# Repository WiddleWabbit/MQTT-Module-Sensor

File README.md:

# MQTT Module - Current Sensors

*Currently In Testing - Not Yet Tested*

This module is a plug-in board for the [MQTT Modular Controller Board](https://github.com/WiddleWabbit/MQTT-ModularControllerBoard). It powers and reads up to three 4-20mA current sensors with high-side sensing at approximately 25V, providing 15-bit resolution measurements.

## Features

- Supports up to 3 x 4-20mA sensors (high-side sensing)
- 15-bit resolution via ADS1115 ADC
- On-board ~25V boost converter from 12V input (TPS61170)
- ATmega328PB microcontroller for local control and communication
- Precision 0.1% shunt resistors with low temperature coefficient (25ppm/°C)
- Basic short-circuit protection using PTCs and TVS diodes
- I2C communication with motherboard and internal ADC

## Architecture

The module is built around an **ATmega328PB-A** microcontroller. It interfaces with the motherboard via I2C (SDA on PE1, SCL on PE0) and uses a dedicated I2C bus for the **ADS1115** ADC (base address 0x48, SDA on PC4, SCL on PC5).

### Power
- Utilises 12V input from motherboard, boosted to ~25V using TI TPS61170 (WEBENCH design) with shielded inductor for reduced EMI
- Powers up to three 4-20mA sensors using this 25V.
- Also utilises the 3.3V from the motherboard.
- Maximum 25V current draw should be less than 200mA.
- Maximum 3.3V current draw should be less than 200mA.

### Sensor Interface
- TP5551 OpAmps in servo configuration for accurate current-to-voltage conversion
- 1.5uF capacitors for signal smoothing
- 0.1% precision shunt resistors with a low 25ppm/°C

### Protection
- PTC resettable fuses on sensors trigger at ~150mA
- TVS diodes for overvoltage clamping (trigger at 13V, clamp to 21.5V)
- Shunt rated for 21.5V for five seconds

### Pinout and Connections
- **Motherboard I2C**: SDA (PE1), SCL (PE0)
- **Internal ADC I2C**: SDA (PC4), SCL (PC5)
- **SNS pin** (motherboard sense): PD4
- **General use modular pin**: PD3
- **ISP Programming Header** (2x3, left to right, top to bottom): MISO, VCC, SCK, MOSI, RESET, GND

## Setup and Build

**Firmware**: Not yet implemented. TBA.

**Programming**:
1. Use the 2x3 ISP header to program the ATmega328PB.
2. Connect to an ISP programmer (e.g., USBasp or Arduino as ISP).
3. Firmware will handle sensor readings, ADC configuration, and I2C communication with the motherboard.

**Assembly**:
- Populate the board per the KiCad project files.
- Ensure proper orientation when plugging into the motherboard slots.

## License

This documentation is part of MQTT-Module-Sensor Project and is licensed under the CERN Open Hardware Licence Version 2 - Permissive (CERN-OHL-P-2.0). 
You may redistribute and modify this documentation under the terms of the CERN-OHL-P-2.0. 
This documentation is distributed WITHOUT ANY EXPRESS OR IMPLIED WARRANTY, INCLUDING OF MERCHANTABILITY, SATISFACTORY QUALITY AND FITNESS FOR A PARTICULAR PURPOSE. See the CERN-OHL-P-2.0 for applicable conditions.

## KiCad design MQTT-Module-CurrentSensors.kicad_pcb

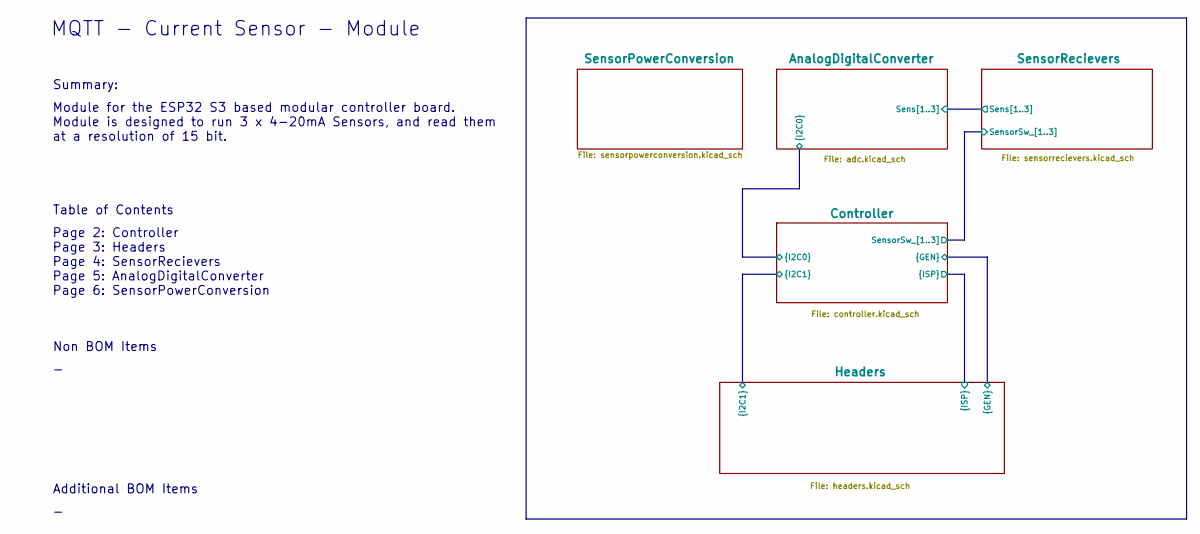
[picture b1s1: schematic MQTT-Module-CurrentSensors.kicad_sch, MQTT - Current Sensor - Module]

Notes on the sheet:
MQTT - Current Sensor - Module
Additional BOM Items
Summary:
Non BOM Items
Page 2: Controller Page 3: Headers Page 4: SensorRecievers Page 5: AnalogDigitalConverter Page 6: SensorPowerConversion
Table of Contents
Module for the ESP32 S3 based modular controller board. Module is designed to run 3 x 4-20mA Sensors, and read them at a resolution of 15 bit.

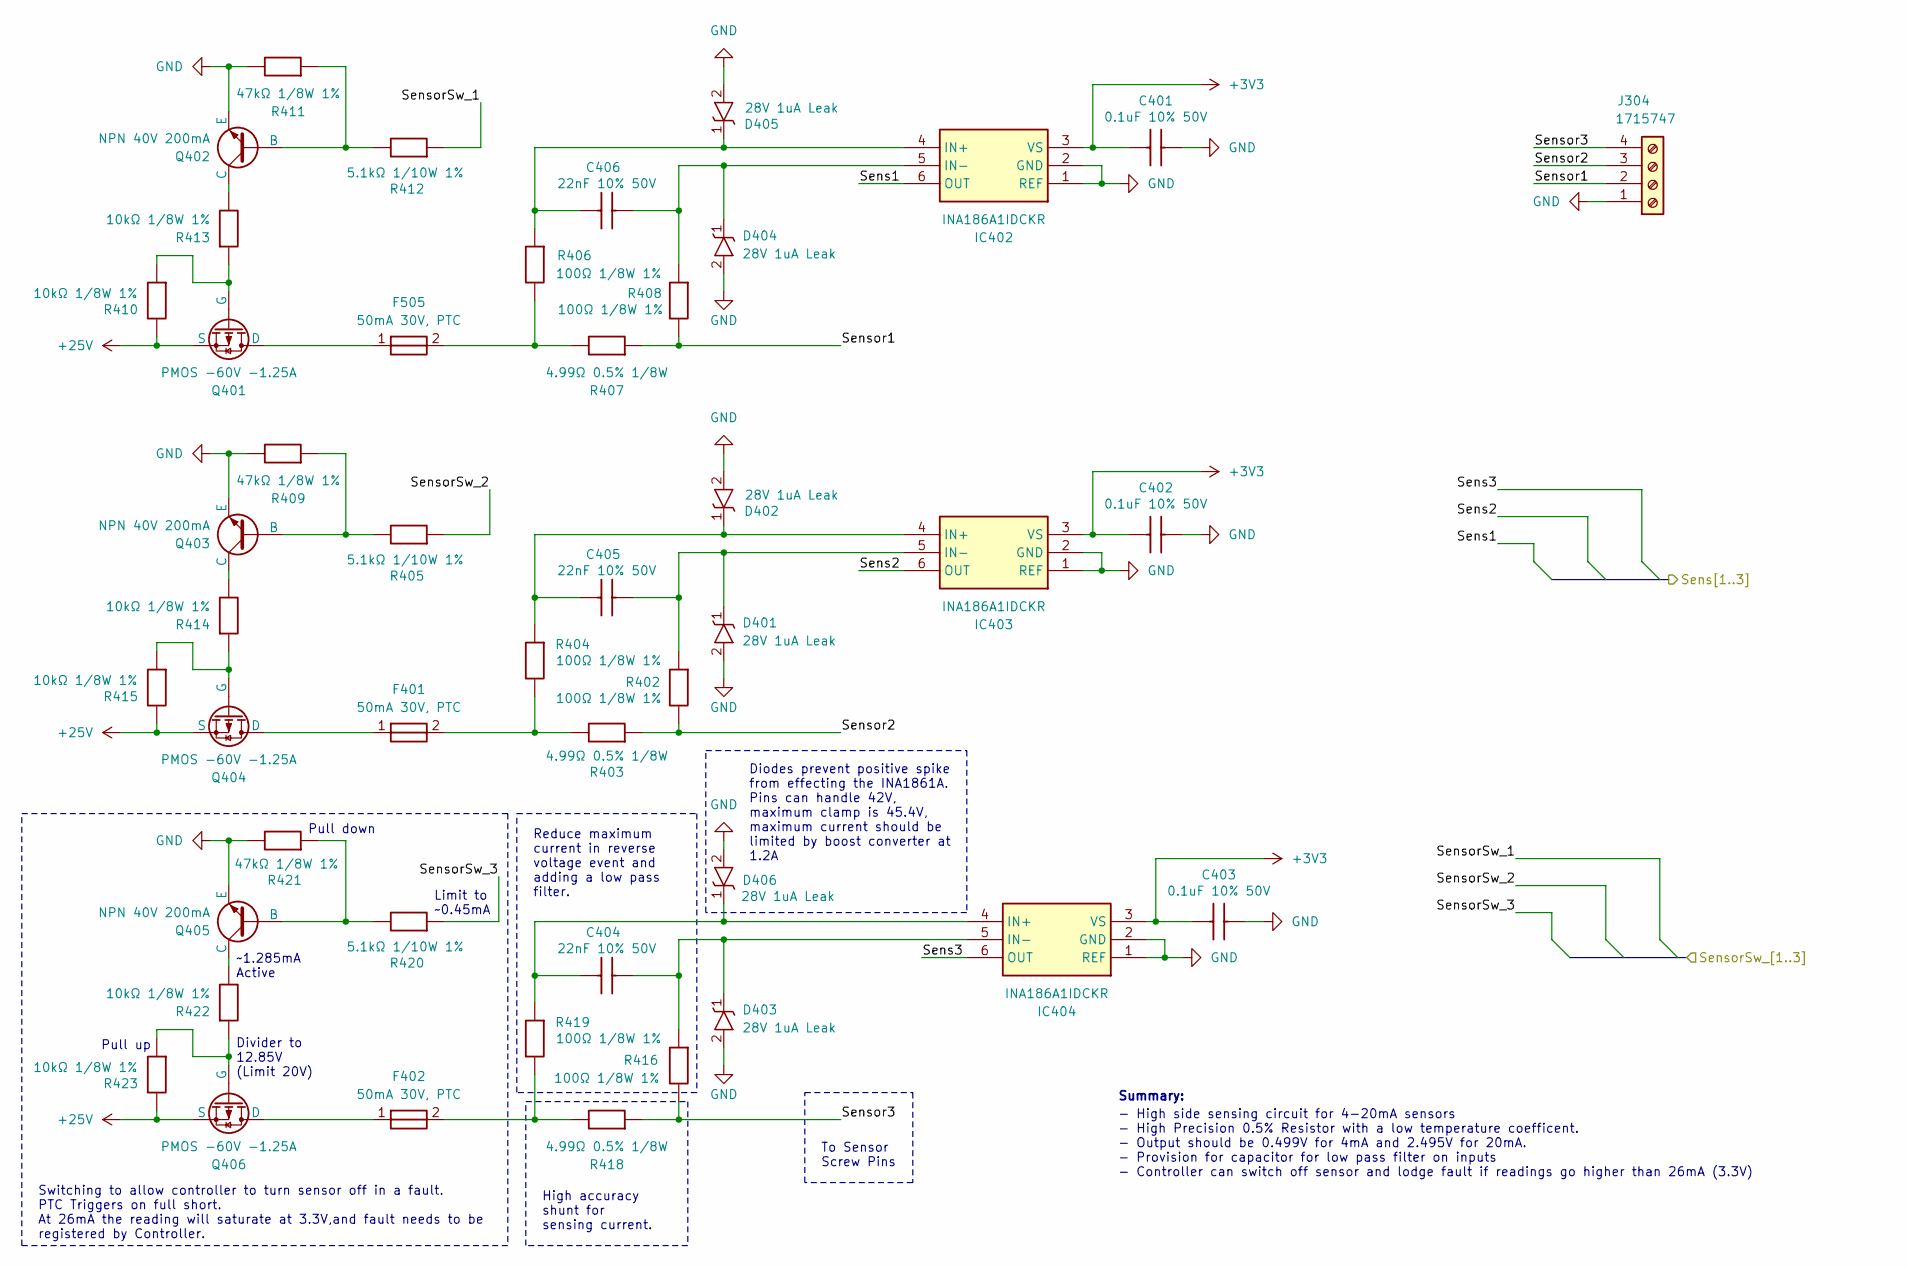
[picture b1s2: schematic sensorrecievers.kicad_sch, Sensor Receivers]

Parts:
C401, C402, C403: 0.1uF 10% 50V; CAPC1608X90N; Mouser Part Number 603-CC603KRX7R9BB104
C404, C405, C406: 22nF 10% 50V; CAPC1608X90N; Manufacturer Part No CL10B223KB8NNNC; JLCPCB Part # C21122
D401, D402, D403, D404, D405, D406: 28V 1uA Leak; SODFL3619X98N; Manufacturer Part No SMF28A; JLCPCB Part # C720061
F401, F402, F505: 50mA 30V, PTC; FUSC3226X110N; Mouser Part Number 652-MF-USMF005-2
IC402, IC403, IC404: INA186A1IDCKR; SOT65P210X110-6N; Mouser Part Number 595-INA186A1IDCKR
J304: 1715747; Mouser Part Number 651-1715747
Q401, Q404, Q406: PMOS -60V -1.25A; SOT-23-3 - FDN5618P; Manufacturer Part No FDN5618P; JLCPCB Part # C400792
Q402, Q403, Q405: NPN 40V 200mA; SOT-23; Manufacturer Part No MMBT3904LT1G; JLCPCB Part # C81464
R402, R404, R406, R408, R416, R419: 100Ω 1/8W 1%; RESC2013X65N; Mouser Part Number 303-0805W8F1000T5E
R403, R407, R418: 4.99Ω 0.5% 1/8W; Generic-0603; Mouser Part Number 71-TNPW06034R99DEEA
R405, R412, R420: 5.1kΩ 1/10W 1%; RESC1608X55N; Mouser Part Number 303-0603WAF5101T5E
R409, R411, R421: 47kΩ 1/8W 1%; RESC2013X65N; Manufacturer Part No 0805W8F4702T5E; JLCPCB Part # C17713
R410, R413, R414, R415, R422, R423: 10kΩ 1/8W 1%; RESC2013X65N; Mouser Part Number 303-0805W8F1002T5E

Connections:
+3V3: C401.1, C402.1, C403.1, IC402.3 (VS), IC403.3 (VS), IC404.3 (VS); also elsewhere on the board
+25V: Q401.2 (S), Q404.2 (S), Q406.2 (S), R410.2, R415.2, R423.2; also elsewhere on the board
/AnalogDigitalConverter/Sens1: IC402.6 (OUT); also elsewhere on the board
/AnalogDigitalConverter/Sens2: IC403.6 (OUT); also elsewhere on the board
/AnalogDigitalConverter/Sens3: IC404.6 (OUT); also elsewhere on the board
/Controller/SensorSw_1: R412.1; also elsewhere on the board
/Controller/SensorSw_2: R405.1; also elsewhere on the board
/Controller/SensorSw_3: R420.1; also elsewhere on the board
/SensorRecievers/Sensor1: J304.2, R407.1, R408.2
/SensorRecievers/Sensor2: J304.3, R402.2, R403.1
/SensorRecievers/Sensor3: J304.4, R416.2, R418.1
GND: C401.2, C402.2, C403.2, D401.2 (A2), D402.2 (A2), D403.2 (A2), D404.2 (A2), D405.2 (A2), D406.2 (A2), IC402.1 (REF), IC402.2 (GND), IC403.1 (REF), IC403.2 (GND), IC404.1 (REF), IC404.2 (GND), J304.1, Q402.2 (E), Q403.2 (E), Q405.2 (E), R409.2, R411.2, R421.2; also elsewhere on the board
unnamed: C405.2, D401.1 (A1), IC403.5 (IN-), R402.1
unnamed: C405.1, D402.1 (A1), IC403.4 (IN+), R404.1
unnamed: C404.2, D403.1 (A1), IC404.5 (IN-), R416.1
unnamed: C406.2, D404.1 (A1), IC402.5 (IN-), R408.1
unnamed: C406.1, D405.1 (A1), IC402.4 (IN+), R406.1
unnamed: C404.1, D406.1 (A1), IC404.4 (IN+), R419.1
unnamed: F401.2, R403.2, R404.2
unnamed: F402.2, R418.2, R419.2
unnamed: F505.2, R406.2, R407.2
unnamed: F505.1, Q401.3 (D)
unnamed: Q401.1 (G), R410.1, R413.1
unnamed: Q402.1 (B), R411.1, R412.2
unnamed: Q402.3 (C), R413.2
unnamed: Q403.1 (B), R405.2, R409.1
unnamed: Q403.3 (C), R414.2
unnamed: F401.1, Q404.3 (D)
unnamed: Q404.1 (G), R414.1, R415.1
unnamed: Q405.1 (B), R420.2, R421.1
unnamed: Q405.3 (C), R422.2
unnamed: F402.1, Q406.3 (D)
unnamed: Q406.1 (G), R422.1, R423.1

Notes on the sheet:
Switching to allow controller to turn sensor off in a fault. PTC Triggers on full short. At 26mA the reading will saturate at 3.3V,and fault needs to be registered by Controller.
Pull down
Pull up
Reduce maximum current in reverse voltage event and adding a low pass filter.
Diodes prevent positive spike from effecting the INA1861A. Pins can handle 42V, maximum clamp is 45.4V, maximum current should be limited by boost converter at 1.2A
Limit to ~0.45mA
To Sensor Screw Pins
- High side sensing circuit for 4-20mA sensors - High Precision 0.5% Resistor with a low temperature coefficent. - Output should be 0.499V for 4mA and 2.495V for 20mA. - Provision for capacitor for low pass filter on inputs - Controller can switch off sensor and lodge fault if readings go higher th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
~1.285mA Active
Summary:
High accuracy shunt for sensing current.
Divider to 12.85V (Limit 20V)

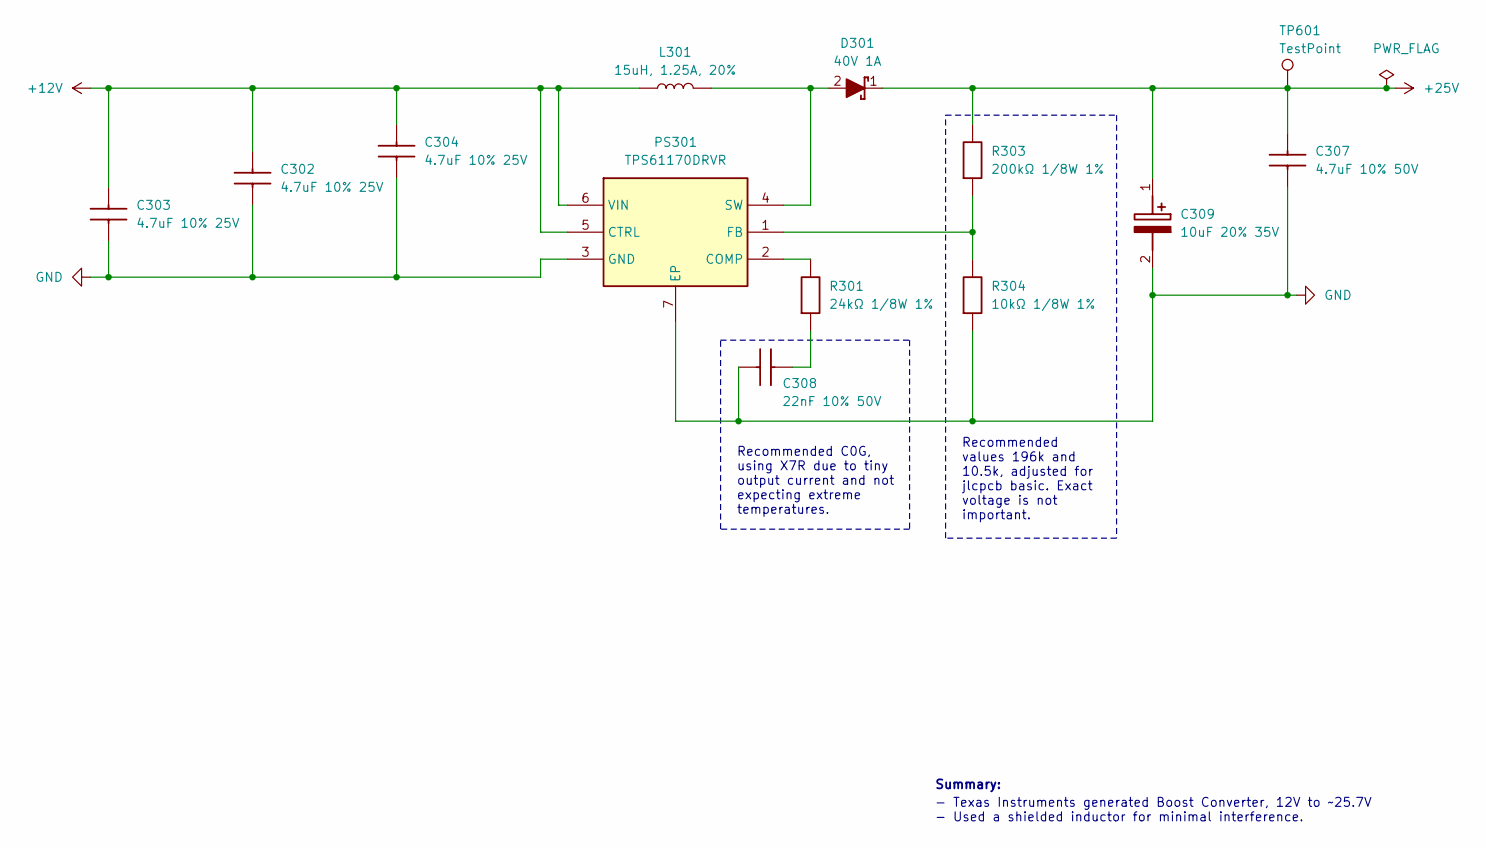
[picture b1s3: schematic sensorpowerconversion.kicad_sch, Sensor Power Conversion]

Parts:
C302, C303, C304: 4.7uF 10% 25V; CAPC2012X140N; Mouser Part Number 187-CL21A475KAQNNNE
C307: 4.7uF 10% 50V; CAPC3216X180N; Manufacturer Part No 1206B475K500NT; JLCPCB Part # C29823
C308: 22nF 10% 50V; CAPC2012X75N; Manufacturer Part No CL21B223KBANNNC; JLCPCB Part # C1729
C309: 10uF 20% 35V; EEE0GA101SR; Mouser Part Number 667-EEE-FK1V100R
D301: 40V 1A; D_SOD-323F; Manufacturer Part No 1N5819WS; JLCPCB Part # C191023
L301: 15uH, 1.25A, 20%; INDM4040X190N; Mouser Part Number 70-IFSC1515AHER150M0
PS301: TPS61170DRVR; SON65P200X200X80-7N; Mouser Part Number 595-TPS61170DRVR
R301: 24kΩ 1/8W 1%; RESC2013X65N; Manufacturer_Part_Number 0805W8F2402T5E; JLCPCB Part # C17575
R303: 200kΩ 1/8W 1%; RESC2013X65N; Manufacturer Part No 0805W8F2003T5E; JLCPCB Part # C17539
R304: 10kΩ 1/8W 1%; RESC2013X65N; Mouser Part Number 303-0805W8F1002T5E
TP601: TestPoint; TestPoint_Pad_2.0x2.0mm

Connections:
+12V: C302.2, C303.2, C304.2, L301.1, PS301.5 (CTRL), PS301.6 (VIN); also elsewhere on the board
+25V: C307.2, C309.1 (+), D301.1 (K), R303.2, TP601.1; also elsewhere on the board
GND: C302.1, C303.1, C304.1, C307.1, C308.1, C309.2 (-), PS301.3 (GND), PS301.7 (EP), R304.1; also elsewhere on the board
unnamed: C308.2, R301.1
unnamed: D301.2 (A), L301.2, PS301.4 (SW)
unnamed: PS301.2 (COMP), R301.2
unnamed: PS301.1 (FB), R303.1, R304.2

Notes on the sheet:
- Texas Instruments generated Boost Converter, 12V to ~25.7V - Used a shielded inductor for minimal interference.
Recommended values 196k and 10.5k, adjusted for jlcpcb basic. Exact voltage is not important.
Recommended C0G, using X7R due to tiny output current and not expecting extreme temperatures.
Summary:

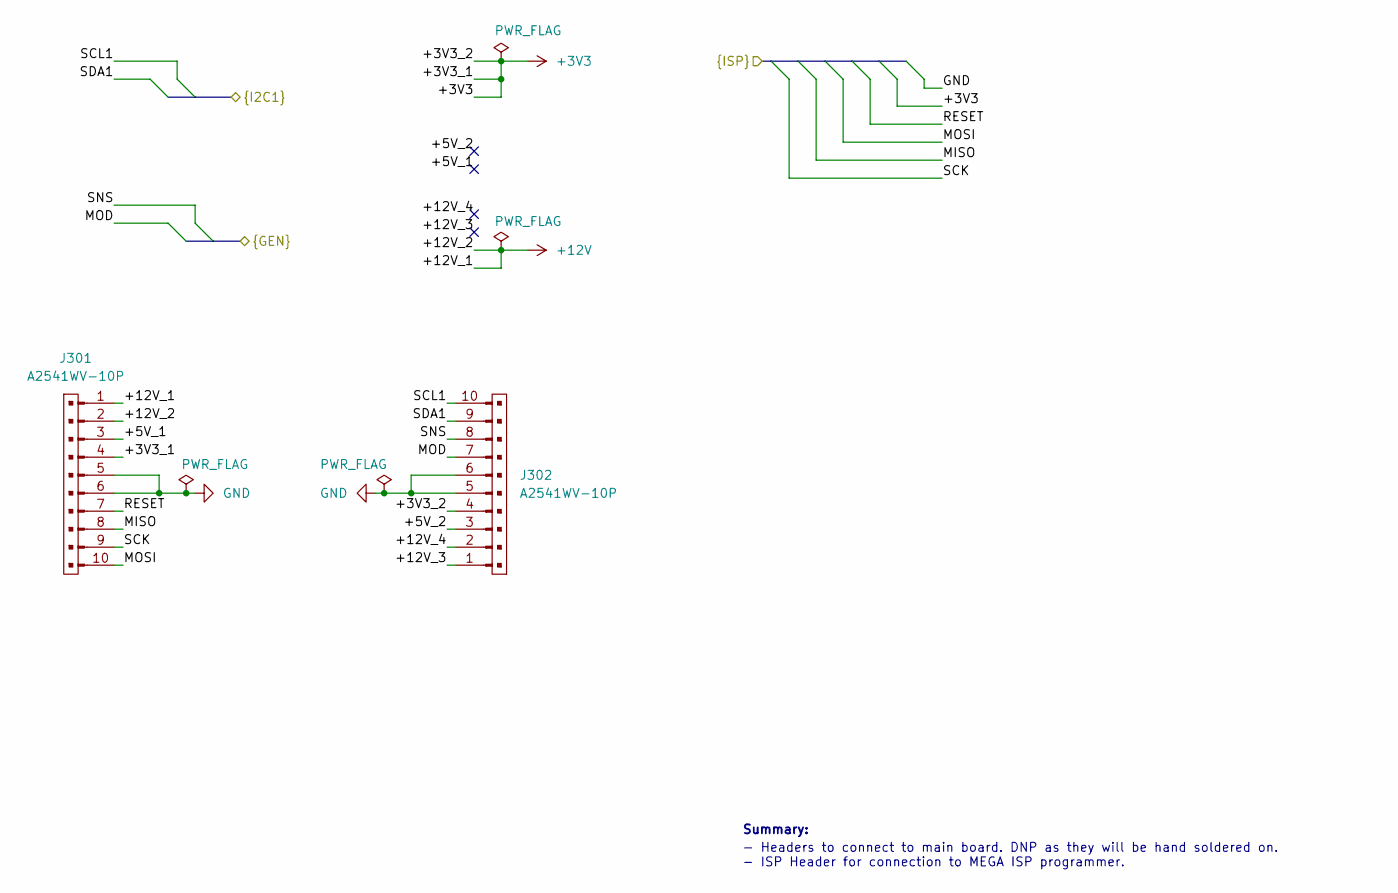
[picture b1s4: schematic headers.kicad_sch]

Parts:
J301, J302: A2541WV-10P; PinHeader_1x10_P2.54mm_Vertical_Male; Manufacturer Part No A2541WV-10P; JLCPCB Part # C225485

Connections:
+3V3: J301.4, J302.4; also elsewhere on the board
+12V: J301.1, J301.2; also elsewhere on the board
/Controller/MISO: J301.8; also elsewhere on the board
/Controller/MOD: J302.7; also elsewhere on the board
/Controller/MOSI: J301.10; also elsewhere on the board
/Controller/RESET: J301.7; also elsewhere on the board
/Controller/SCK: J301.9; also elsewhere on the board
/Controller/SCL1: J302.10; also elsewhere on the board
/Controller/SDA1: J302.9; also elsewhere on the board
/Controller/SNS: J302.8; also elsewhere on the board
/Headers/+5V_1: J301.3
/Headers/+5V_2: J302.3
/Headers/+12V_3: J302.1
/Headers/+12V_4: J302.2
GND: J301.5, J301.6, J302.5, J302.6; also elsewhere on the board

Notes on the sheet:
Summary:
- Headers to connect to main board. DNP as they will be hand soldered on. - ISP Header for connection to MEGA ISP programmer.

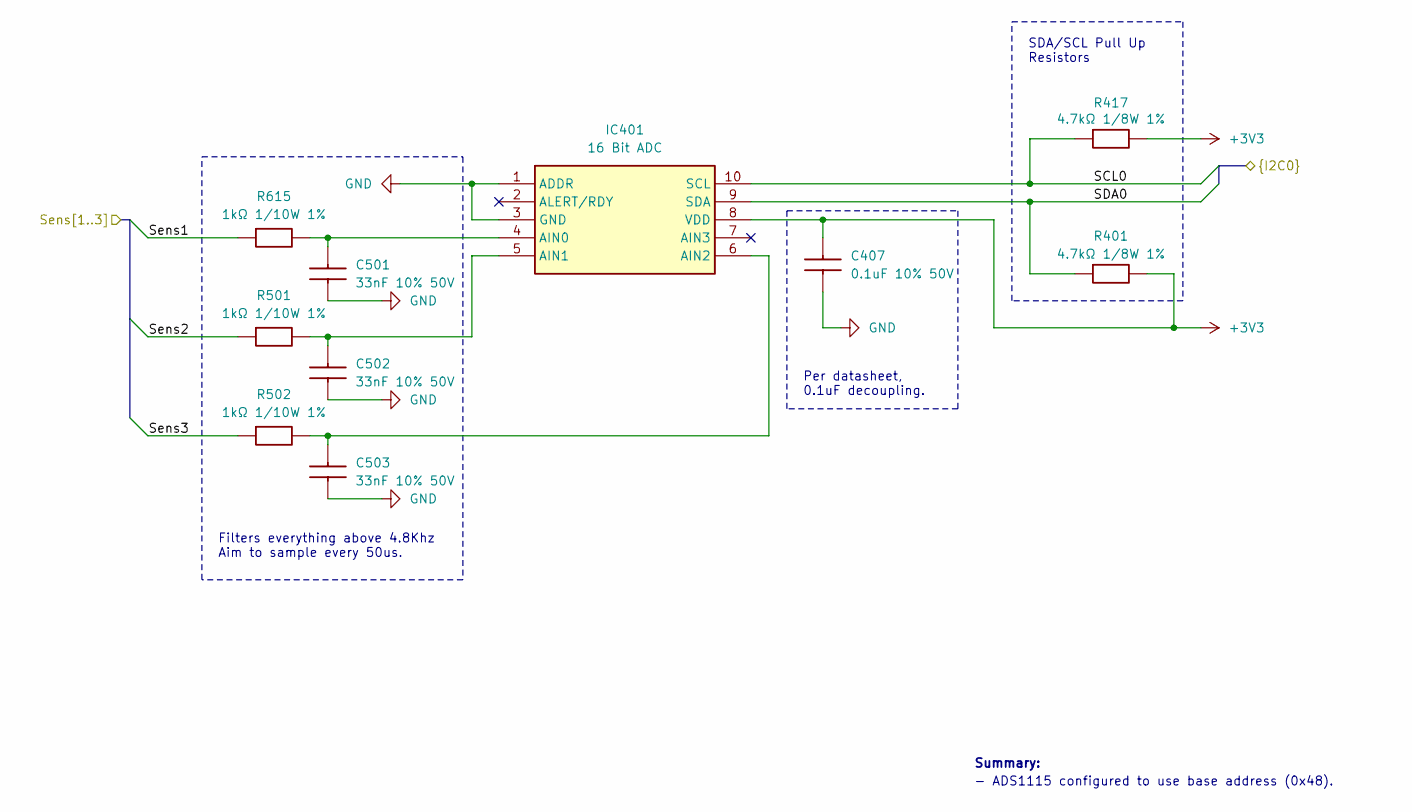
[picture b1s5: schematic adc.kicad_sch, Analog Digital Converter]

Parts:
C407: 0.1uF 10% 50V; CAPC1608X90N; Mouser Part Number 603-CC603KRX7R9BB104
C501, C502, C503: 33nF 10% 50V; CAPC1608X90N; Manufacturer Part No CL10B333KB8NNNC; JLCPCB Part # C21117
IC401: 16 Bit ADC; SOP50P490X110-10N; Mouser Part Number 595-ADS1115IDGST
R401, R417: 4.7kΩ 1/8W 1%; RESC2013X65N; Mouser Part Number 303-0805W8F4701T5E
R501, R502, R615: 1kΩ 1/10W 1%; RESC1608X55N; Manufacturer Part No 0603WAF1001T5E; JLCPCB Part # C21190

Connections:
+3V3: C407.2, IC401.8 (VDD), R401.2, R417.2; also elsewhere on the board
/AnalogDigitalConverter/SCL0: IC401.10 (SCL), R417.1; also elsewhere on the board
/AnalogDigitalConverter/SDA0: IC401.9 (SDA), R401.1; also elsewhere on the board
/AnalogDigitalConverter/Sens1: R615.1; also elsewhere on the board
/AnalogDigitalConverter/Sens2: R501.1; also elsewhere on the board
/AnalogDigitalConverter/Sens3: R502.1; also elsewhere on the board
GND: C407.1, C501.1, C502.1, C503.1, IC401.1 (ADDR), IC401.3 (GND); also elsewhere on the board
unnamed: C501.2, IC401.4 (AIN0), R615.2
unnamed: C502.2, IC401.5 (AIN1), R501.2
unnamed: C503.2, IC401.6 (AIN2), R502.2

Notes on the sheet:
Filters everything above 4.8Khz Aim to sample every 50us.
SDA/SCL Pull Up Resistors
- ADS1115 configured to use base address (0x48).
Per datasheet, 0.1uF decoupling.
Summary:

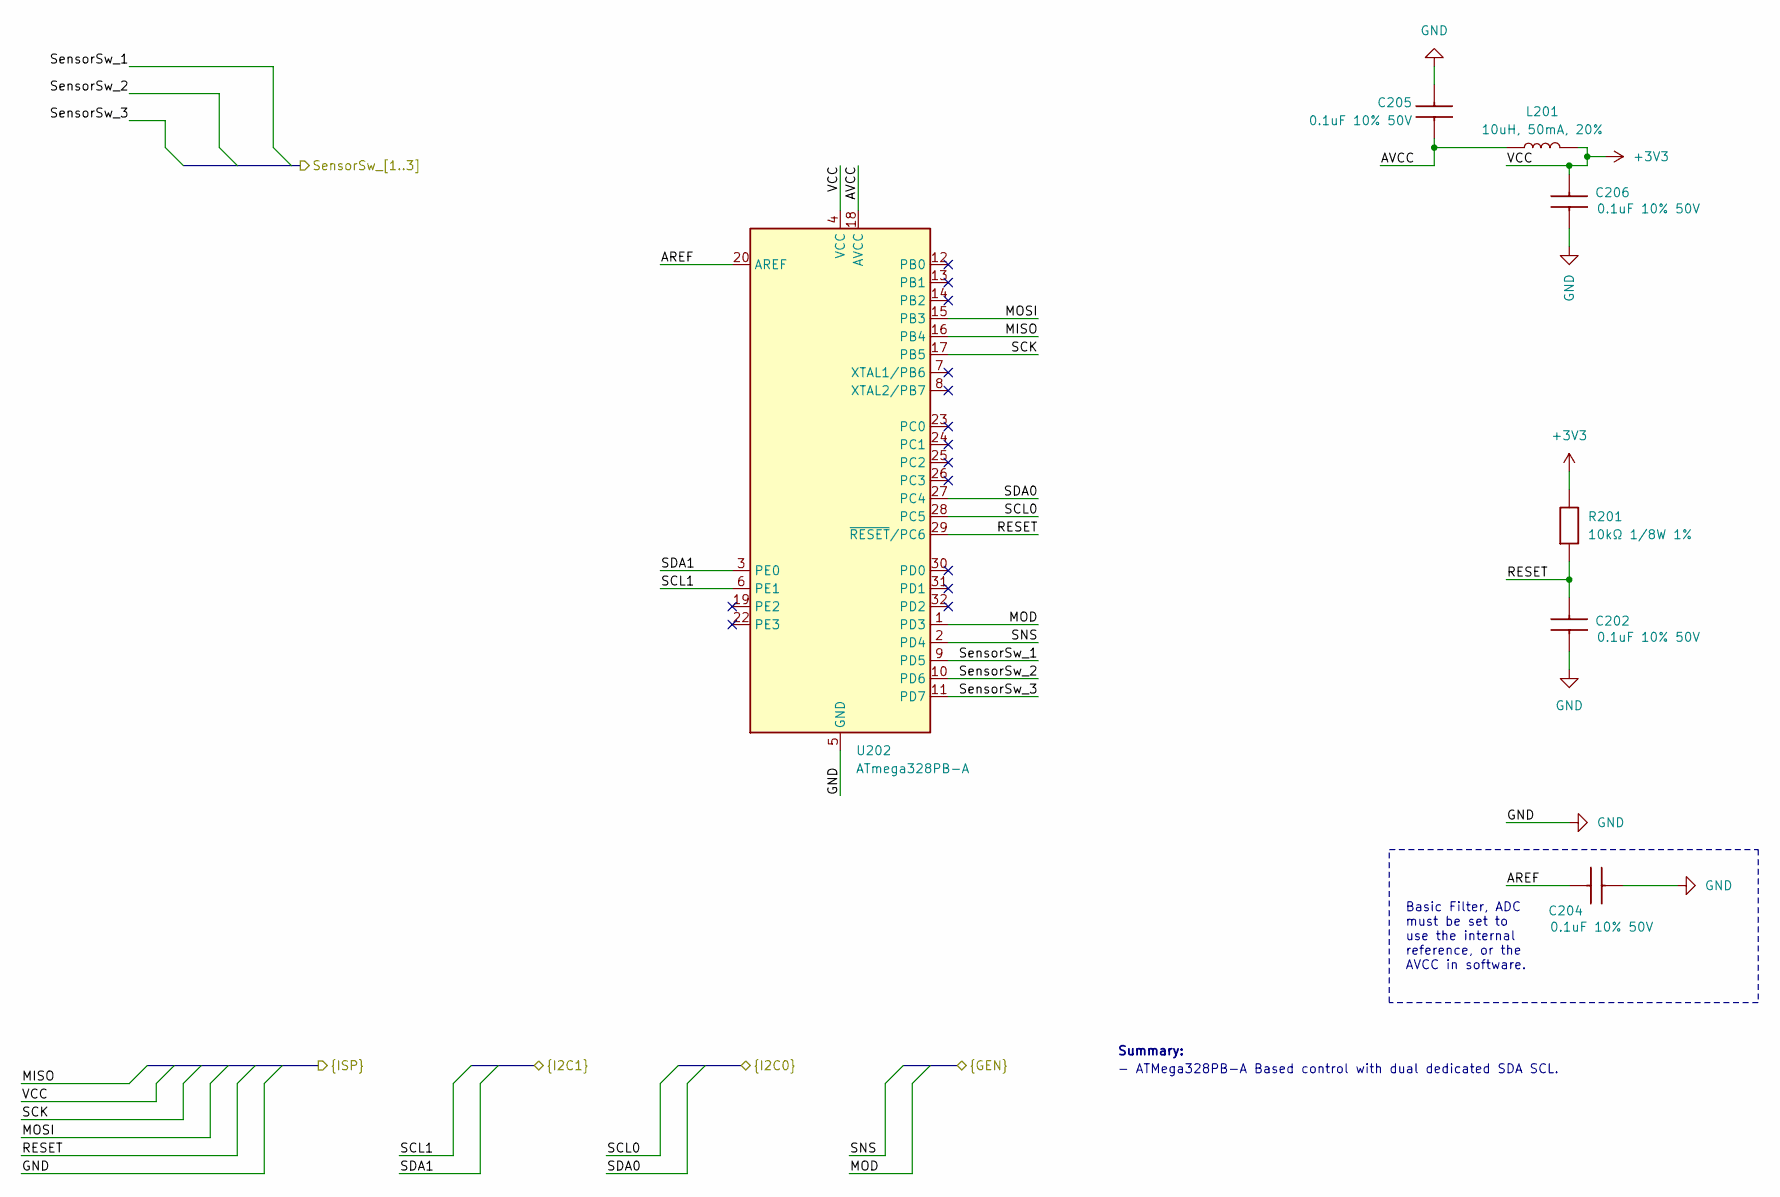
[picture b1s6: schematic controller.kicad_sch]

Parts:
C202, C204, C205, C206: 0.1uF 10% 50V; CAPC1608X90N; Mouser Part Number 603-CC603KRX7R9BB104
L201: 10uH, 50mA, 20%; L_0603_1608Metric; Manufacturer Part No MCL1608S100MT; JLCPCB Part # C51942
R201: 10kΩ 1/8W 1%; RESC2013X65N; Mouser Part Number 303-0805W8F1002T5E
U202: ATmega328PB-A; TQFP-32_7x7mm_P0.8mm; Manufacturer Part No ATMEGA328PB-AU; JLCPCB Part # C132230

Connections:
+3V3: C206.2, L201.2, R201.2, U202.4 (VCC); also elsewhere on the board
/AnalogDigitalConverter/SCL0: U202.28 (PC5); also elsewhere on the board
/AnalogDigitalConverter/SDA0: U202.27 (PC4); also elsewhere on the board
/Controller/AREF: C204.1, U202.20 (AREF)
/Controller/AVCC: C205.1, L201.1, U202.18 (AVCC)
/Controller/MISO: U202.16 (PB4); also elsewhere on the board
/Controller/MOD: U202.1 (PD3); also elsewhere on the board
/Controller/MOSI: U202.15 (PB3); also elsewhere on the board
/Controller/RESET: C202.1, R201.1, U202.29 (~RESET/PC6); also elsewhere on the board
/Controller/SCK: U202.17 (PB5); also elsewhere on the board
/Controller/SCL1: U202.6 (PE1); also elsewhere on the board
/Controller/SDA1: U202.3 (PE0); also elsewhere on the board
/Controller/SNS: U202.2 (PD4); also elsewhere on the board
/Controller/SensorSw_1: U202.9 (PD5); also elsewhere on the board
/Controller/SensorSw_2: U202.10 (PD6); also elsewhere on the board
/Controller/SensorSw_3: U202.11 (PD7); also elsewhere on the board
GND: C202.2, C204.2, C205.2, C206.1, U202.5 (GND), U202.21 (GND); also elsewhere on the board

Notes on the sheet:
Basic Filter, ADC must be set to use the internal reference, or the AVCC in software.
- ATMega328PB-A Based control with dual dedicated SDA SCL.
Summary:

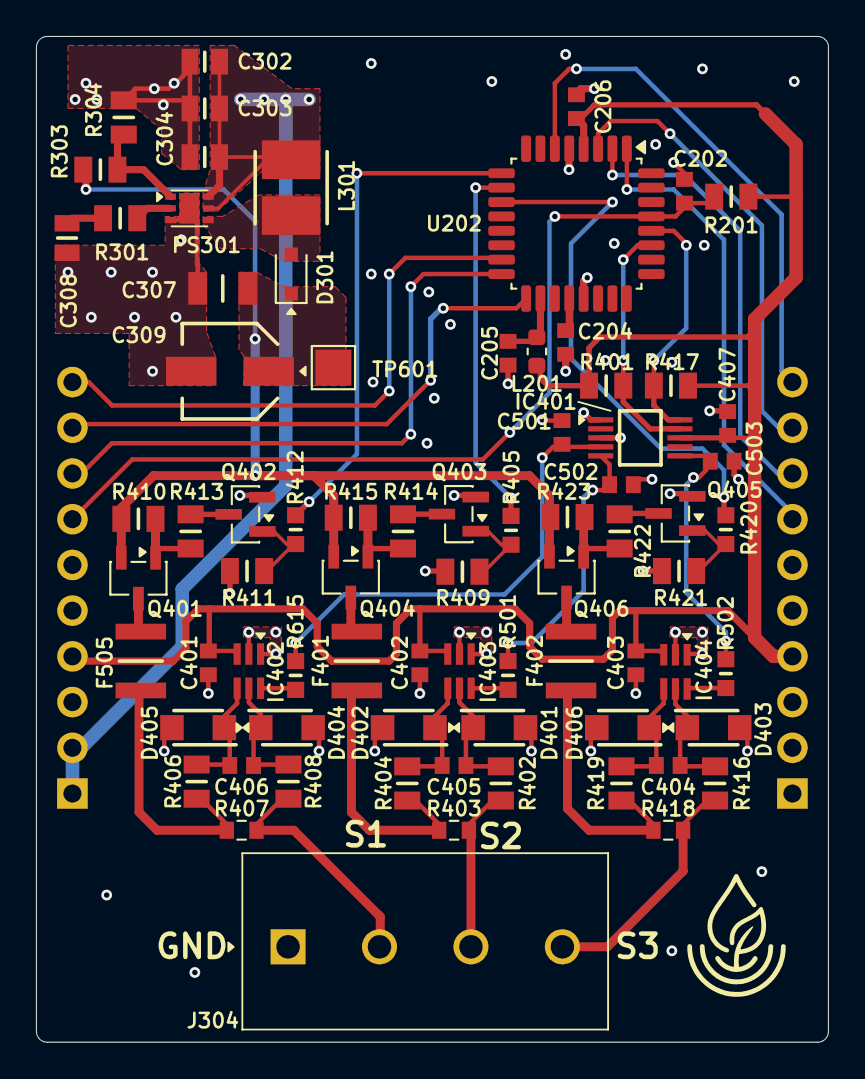
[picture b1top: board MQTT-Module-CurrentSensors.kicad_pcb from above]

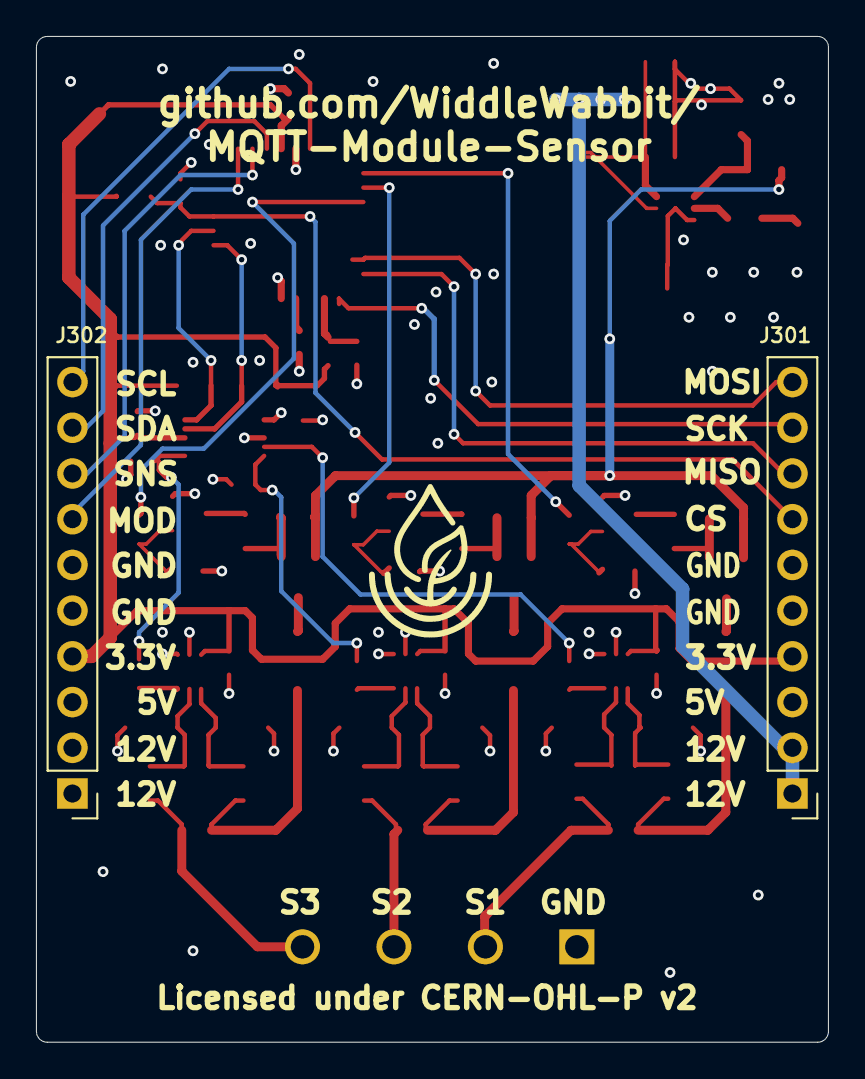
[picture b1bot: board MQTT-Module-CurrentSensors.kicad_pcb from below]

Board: 4 copper layers, 44.0 x 55.9 mm, 78 parts (2 on the bottom side), 53 nets.

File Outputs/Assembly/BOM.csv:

"#","Qty","Reference","Value","Manufacturer","Manufacturer Part No","JLCPCB Part #","Package","Footprint"
"1","8","C202,C204,C205,C206,C401,C402,C403,C407","0.1uF 10% 50V","YAGEO","CC0603KRX7R9BB104","C14663","0603","JLCPCB Basic:CAPC1608X90N"
"2","3","C302,C303,C304","4.7uF 10% 25V","Samsung Electro-Mechanics","CL21A475KAQNNNE","C1779","0805","JLCPCB Basic:CAPC2012X140N"
"3","1","C307","4.7uF 10% 50V","FH (Guangdong Fenghua Advanced Tech)","1206B475K500NT","C29823","1206","JLCPCB Basic:CAPC3216X180N"
"4","1","C308","22nF 10% 50V","Samsung Electro-Mechanics","CL21B223KBANNNC","C1729","0805","JLCPCB Basic:CAPC2012X75N"
"5","1","C309","10uF 20% 35V","PANASONIC","EEEFK1V100R","C336198","SMD","PANASONIC Capacitors:EEE0GA101SR"
"6","3","C404,C405,C406","22nF 10% 50V","Samsung Electro-Mechanics","CL10B223KB8NNNC","C21122","0603","JLCPCB Basic:CAPC1608X90N"
"7","3","C501,C502,C503","33nF 10% 50V","Samsung Electro-Mechanics","CL10B333KB8NNNC","C21117","0603","JLCPCB Basic:CAPC1608X90N"
"8","1","D301","40V 1A","Guangdong Hottech","1N5819WS","C191023","SOD-323","GUANGDONG HOTTECH Diodes:D_SOD-323F"
"9","6","D401,D402,D403,D404,D405,D406","28V 1uA Leak","Littelfuse","SMF28A","C720061","SOD-123FL","LITTELFUSE Diodes:SODFL3619X98N"
"10","3","F401,F402,F505","50mA 30V, PTC","BOURNS","MF-USMF005-2","C118758","1210","BOURNS Fuses:FUSC3226X110N"
"11","1","IC401","16 Bit ADC","Texas Instruments","ADS1115IDGST","C468683","VSSOP-10-0.5mm","TEXAS INSTRUMENTS ICs:SOP50P490X110-10N"
"12","3","IC402,IC403,IC404","INA186A1IDCKR","TI","INA186A1IDCKR","C2058311","SC-70-6","TEXAS INSTRUMENTS ICs:SOT65P210X110-6N"
"13","2","J301,J302","A2541WV-10P","CJT(Changjiang Connectors)","A2541WV-10P","C225485","Plugin,P=2.54mm","CJT Connectors:PinHeader_1x10_P2.54mm_Vertical_Male"
"14","1","J304","1715747","Phoenix Contact","1715747","C5443561","P=5.08mm","PHOENIX CONTACT Terminals:1715747"
"15","1","L201","10uH, 50mA, 20%","Sunlord","MCL1608S100MT","C51942","0603","SUNLORD Inductors:L_0603_1608Metric"
"16","1","L301","15uH, 1.25A, 20%","Vishay Intertech","IFSC1515AHER150M01","C844950","SMD,4x4mm","VISHAY INTERTECH Inductors:INDM4040X190N"
"17","1","PS301","TPS61170DRVR","Texas Instruments","TPS61170DRVR","C15163","WSON-6(2x2)","TEXAS INSTRUMENTS ICs:SON65P200X200X80-7N"
"18","3","Q401,Q404,Q406","PMOS -60V -1.25A","onsemi","FDN5618P","C400792","SOT-23-3","ONSEMI Transistors:SOT-23-3 - FDN5618P"
"19","3","Q402,Q403,Q405","NPN 40V 200mA","onsemi","MMBT3904LT1G","C81464","SOT-23","ONSEMI Transistors:SOT-23"
"20","8","R201,R304,R410,R413,R414,R415,R422,R423","10kΩ 1/8W 1%","UNI-ROYAL(Uniroyal Elec)","0805W8F1002T5E","C17414","0805","JLCPCB Basic:RESC2013X65N"
"21","1","R301","24kΩ 1/8W 1%","UNI-ROYAL(Uniroyal Elec)","0805W8F2402T5E","C17575","0805","JLCPCB Basic:RESC2013X65N"
"22","1","R303","200kΩ 1/8W 1%","UNI-ROYAL(Uniroyal Elec)","0805W8F2003T5E","C17539","0805","JLCPCB Basic:RESC2013X65N"
"23","2","R401,R417","4.7kΩ 1/8W 1%","UNI-ROYAL(Uniroyal Elec)","0805W8F4701T5E"," C17673","0805","JLCPCB Basic:RESC2013X65N"
"24","6","R402,R404,R406,R408,R416,R419","100Ω 1/8W 1%","UNI-ROYAL(Uniroyal Elec)","0805W8F1000T5E","C17408","0805","JLCPCB Basic:RESC2013X65N"
"25","3","R403,R407,R418","4.99Ω 0.5% 1/8W","Vishay Intertech","TNPW06034R99DEEA","C1857702","0603","JLCPCB Basic:Generic-0603"
"26","3","R405,R412,R420","5.1kΩ 1/10W 1%","UNI-ROYAL(Uniroyal Elec)","0603WAF5101T5E","C23186","0603","JLCPCB Basic:RESC1608X55N"
"27","3","R409,R411,R421","47kΩ 1/8W 1%","UNI-ROYAL(Uniroyal Elec)","0805W8F4702T5E","C17713","0805","JLCPCB Basic:RESC2013X65N"
"28","3","R501,R502,R615","1kΩ 1/10W 1%","UNI-ROYAL(Uniroyal Elec)","0603WAF1001T5E","C21190","0603","JLCPCB Basic:RESC1608X55N"
"29","1","U202","ATmega328PB-A","Microchip Tech","ATMEGA328PB-AU","C132230","TQFP-32(7x7)","Package_QFP:TQFP-32_7x7mm_P0.8mm"

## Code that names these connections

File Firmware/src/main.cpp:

#include <Arduino.h>

#include "AvrAds1115.h"
#include "AvrEeprom.h"
#include "AvrInterruptMask.h"
#include "AvrSensorSwitchPort.h"
#include "AvrTwi1Slave.h"
#include "ModuleLink.h"
#include "ModuleProtocol.h"
#include "SensorInputs.h"


// ========== Board pins ==========

// Motherboard bus is schematic I2C1. It is the chip's TWI1 peripheral:
// PE0 is SDA and PE1 is SCL. Wire1 owns these pins in hardware.
const uint8_t SDA_PIN = 23;
const uint8_t SCL_PIN = 24;
const uint8_t MOD_PIN = 3;
const uint8_t SNS_PIN = 4;

// SensorSw drives the NPN that turns on that channel's high-side PMOS.
// High closes the loop. The base pulldown holds it open until a set-on.
const uint8_t SENSOR_SW1_PIN = 5;
const uint8_t SENSOR_SW2_PIN = 6;
const uint8_t SENSOR_SW3_PIN = 7;

// ADC bus is schematic I2C0. It is the chip's TWI0 peripheral.
// PC4 is SDA and PC5 is SCL. Wire owns these pins in hardware.
const uint8_t ADC_SDA_PIN = 18;
const uint8_t ADC_SCL_PIN = 19;

static_assert(SDA_PIN == 23, "PE0 is motherboard SDA.");
static_assert(SCL_PIN == 24, "PE1 is motherboard SCL.");
static_assert(MOD_PIN == 3, "PD3 is MOD.");
static_assert(SNS_PIN == 4, "PD4 is SNS.");
static_assert(SENSOR_SW1_PIN == 5, "PD5 is SensorSw_1.");
static_assert(SENSOR_SW2_PIN == 6, "PD6 is SensorSw_2.");
static_assert(SENSOR_SW3_PIN == 7, "PD7 is SensorSw_3.");
static_assert(ADC_SDA_PIN == 18, "PC4 is ADC SDA.");
static_assert(ADC_SCL_PIN == 19, "PC5 is ADC SCL.");


// ========== Product settings ==========

const uint16_t MODULE_TYPE = module_protocol::kTypeSensorModule;

// Identity firmware bytes are board revision, then firmware revision.
const uint8_t BOARD_REVISION = 3;
const uint8_t FIRMWARE_REVISION = 1;
const uint16_t FIRMWARE_VERSION =
    static_cast<uint16_t>((static_cast<uint16_t>(BOARD_REVISION) << 8) |
                          FIRMWARE_REVISION);

// ADDR is strapped to GND on this board.
const uint8_t ADS1115_ADDRESS = 0x48;
const uint8_t SENSOR_COUNT = 3;

// 2400 counts is 0.300 V at GAIN_ONE (125 uV per count). On the
// 4.99 ohm shunt and INA186A1 (25 V/V) that is about 2.4 mA. A live
// 4 mA loop is 3992 counts. An open input sits below this.
const int16_t SENSOR_CONNECTED_MIN_COUNTS = 2400;

// 21956 counts is 2.745 V, 22 mA on that same front end. Two stored
// samples at or above this open the loop and latch a fault.
const int32_t SENSOR_TRIP_COUNTS = 21956;
const uint8_t SENSOR_TRIP_SAMPLES = 2;

// Live samples kept for each input's reading. The window rotates
// once it is full. A shorter run reports the average so far.
const uint8_t SENSOR_AVERAGE_SAMPLES = 25;


// ========== Modules ==========

AvrTwi1Slave moduleSlave;
AvrAds1115 ads(ADS1115_ADDRESS, AvrAds1115::kGainOne,
               AvrAds1115::kRate860Sps);
AvrSensorSwitchPort sensorSwitches(SENSOR_SW1_PIN, SENSOR_SW2_PIN,
                                   SENSOR_SW3_PIN);
AvrInterruptMask interruptMask;
AvrEeprom eeprom;
SensorInputs sensorInputs(ads, sensorSwitches, interruptMask, eeprom,
                          SENSOR_COUNT, SENSOR_CONNECTED_MIN_COUNTS,
                          SENSOR_TRIP_COUNTS, SENSOR_TRIP_SAMPLES,
                          SENSOR_AVERAGE_SAMPLES);
ModuleLink moduleLink(moduleSlave, sensorInputs, MODULE_TYPE, FIRMWARE_VERSION);


// ========== Application ==========

/**
 * Drives SNS low so the motherboard sees this module seated, drives
 * each SensorSw pin low so every loop stays open, and holds MOD as an
 * input with pull-up. The slave stays off until MOD is low. A loop
 * closes only after SET_SENSOR on.
 *
 * @return Nothing.
 */
void setup()
{
  pinMode(SNS_PIN, OUTPUT);
  digitalWrite(SNS_PIN, LOW);
  pinMode(MOD_PIN, INPUT_PULLUP);
  sensorSwitches.begin();
}

/**
 * Advances the ADS1115 scan one step, which also arms at most one
 * fault-image byte, then gates the unconfigured address on MOD. A
 * low MOD enables 0x0A. After SET_ADDRESS the link keeps that
 * address. This loop does not block, so the host's 5 ms MOD gate
 * is met.
 *
 * @return Nothing.
 */
void loop()
{
  sensorInputs.update();
  const bool modIsLow = digitalRead(MOD_PIN) == LOW;
  moduleLink.update(modIsLow);
}

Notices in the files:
MQTT-Module-CurrentSensors.kicad_pcb:
Licensed under CERN-OHL-P v2
